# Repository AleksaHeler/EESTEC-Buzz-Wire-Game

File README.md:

# EESTEC-Buzz-Wire-Game

Buzz wire game HW for interactive booths made for EESTEC LC Novi Sad. Made in KiCAD and order from PCB manufaturer from China.

## Example

## Idea

Idea is to make a simple custom HW board for visitors to play with and learn some basic electronics examples.

Using 555 timer chip create an oscillator which beeps a piezo buzzer when wires touch.

## Execution

TODO: add images:
 - schematic
 - PCB (KiCAD view, photos of actual PCBs)
 - board, mounting of all components

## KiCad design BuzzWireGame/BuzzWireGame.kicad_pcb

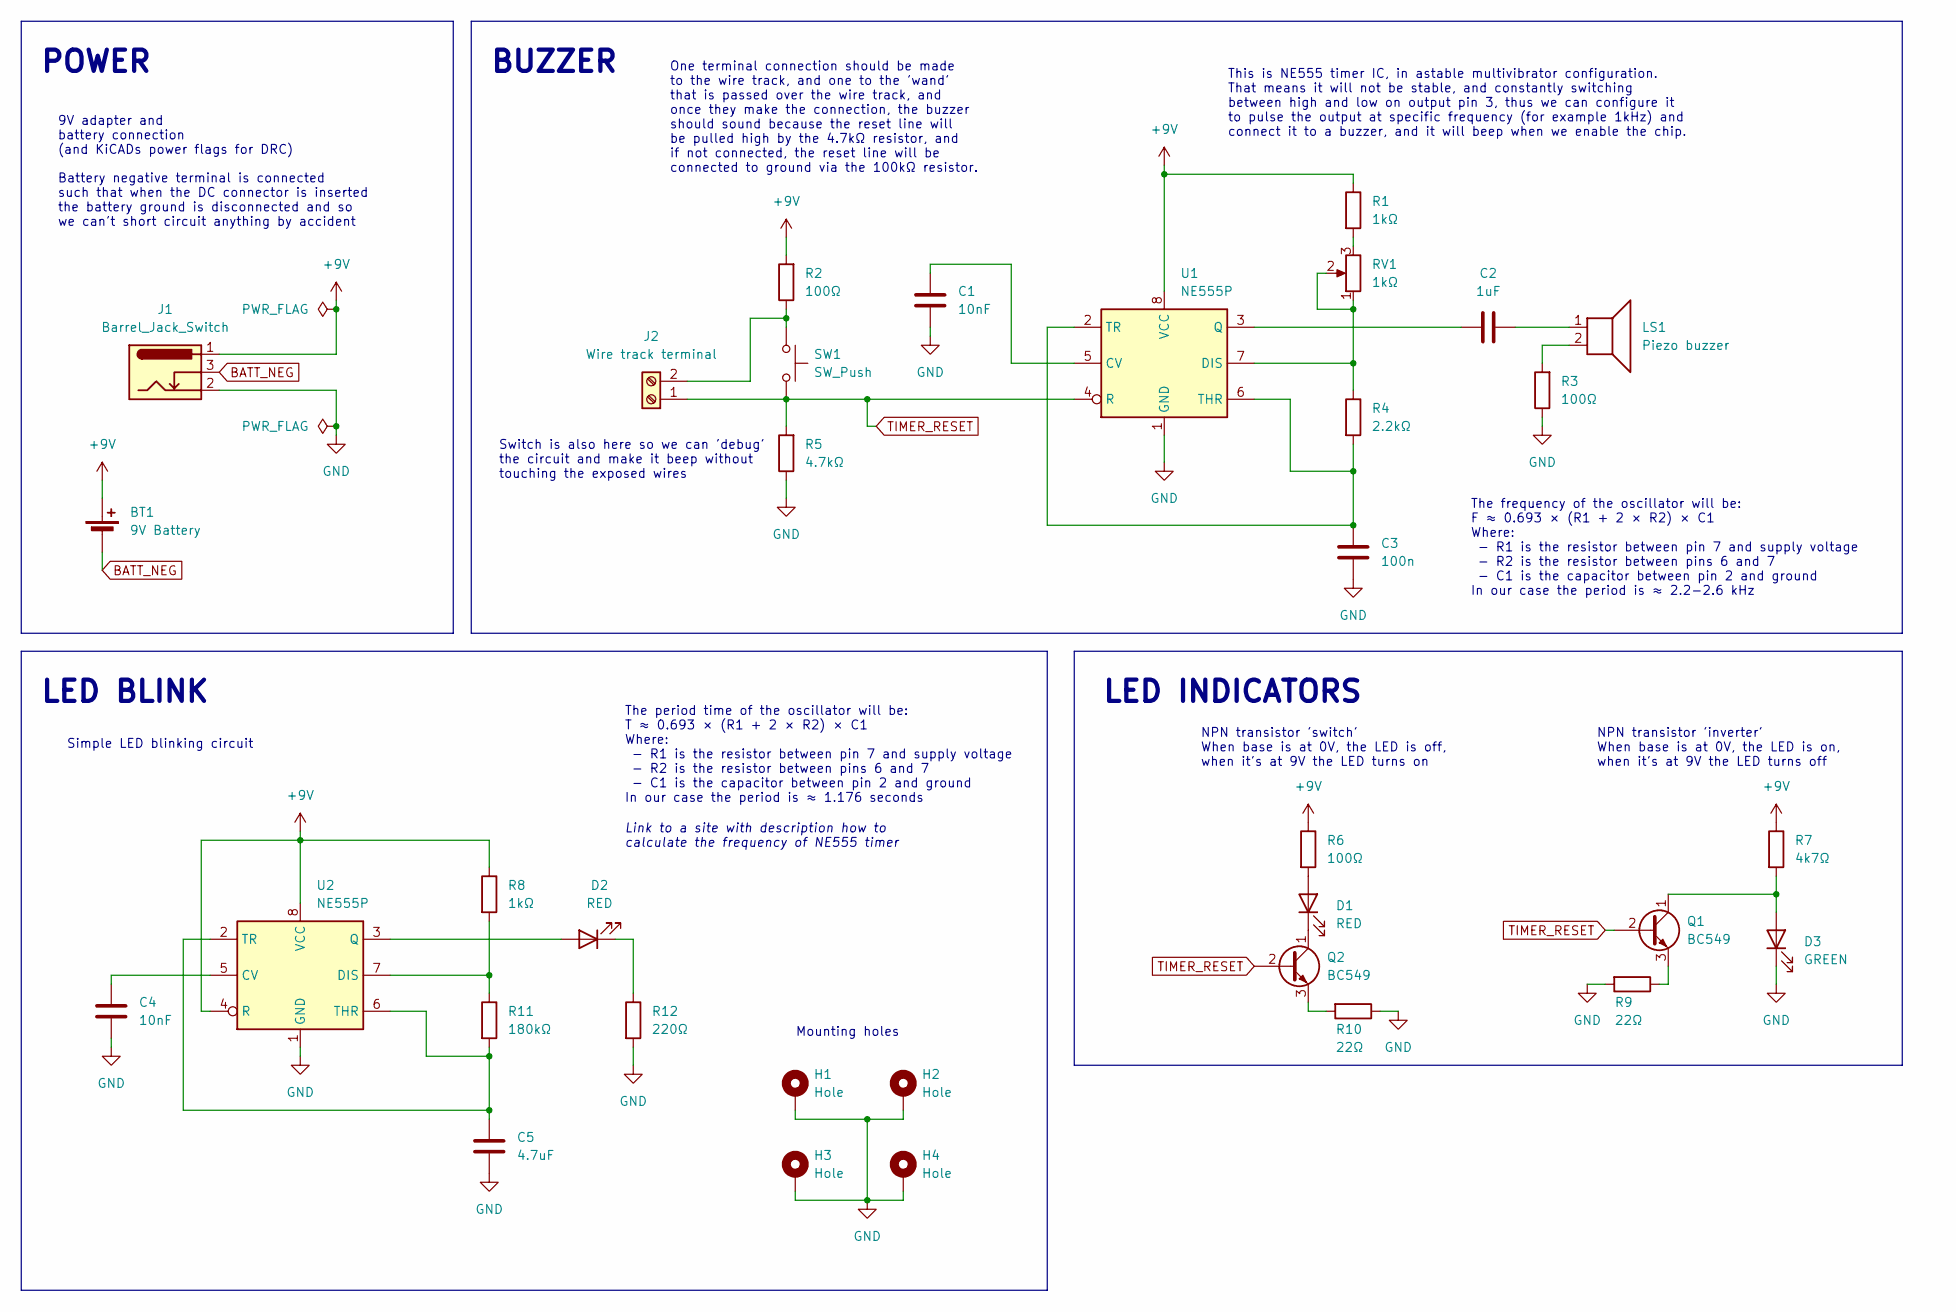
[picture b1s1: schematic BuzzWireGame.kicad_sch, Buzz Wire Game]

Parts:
BT1: 9V Battery; TerminalBlock_bornier-2_P5.08mm
C1, C4: 10nF; C_1206_3216Metric
C2: 1uF; C_1206_3216Metric
C3: 100n; C_1206_3216Metric
C5: 4.7uF; CP_Radial_D4.0mm_P2.00mm
D1, D2: RED; LED_D5.0mm_Clear
D3: GREEN; LED_D5.0mm_Clear
H1, H2, H3, H4: Hole; MountingHole_3.2mm_M3_Pad_Via
J1: Barrel_Jack_Switch; BarrelJack_Horizontal
J2: Wire track terminal; TerminalBlock_bornier-2_P5.08mm
LS1: Piezo buzzer; Indicator_PUI_AI-1440-TWT-24V-2-R
Q1, Q2: BC549; TO-92_Inline
R1, R8: 1kΩ; R_Axial_DIN0207_L6.3mm_D2.5mm_P10.16mm_Horizontal
R2, R3, R6: 100Ω; R_Axial_DIN0207_L6.3mm_D2.5mm_P10.16mm_Horizontal
R4: 2.2kΩ; R_Axial_DIN0207_L6.3mm_D2.5mm_P10.16mm_Horizontal
R5: 4.7kΩ; R_Axial_DIN0207_L6.3mm_D2.5mm_P10.16mm_Horizontal
R7: 4k7Ω; R_Axial_DIN0207_L6.3mm_D2.5mm_P10.16mm_Horizontal
R9, R10: 22Ω; R_Axial_DIN0207_L6.3mm_D2.5mm_P10.16mm_Horizontal
R11: 180kΩ; R_Axial_DIN0207_L6.3mm_D2.5mm_P10.16mm_Horizontal
R12: 220Ω; R_Axial_DIN0207_L6.3mm_D2.5mm_P10.16mm_Horizontal
RV1: 1kΩ; Potentiometer_Alps_RK163_Single_Horizontal
SW1: SW_Push; SW_PUSH_6mm_H4.3mm
U1, U2: NE555P; DIP-8_W7.62mm

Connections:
+9V: BT1.1 (+), J1.1, R1.1, R2.2, R6.1, R7.1, R8.1, U1.8 (VCC), U2.4 (R), U2.8 (VCC)
BATT_NEG: BT1.2 (-), J1.3
GND: C1.2, C3.2, C4.2, C5.2, D3.1 (K), H1.1, H2.1, H3.1, H4.1, J1.2, R3.1, R5.1, R9.2, R10.1, R12.2, U1.1 (GND), U2.1 (GND)
unnamed: C2.2, LS1.1
unnamed: D1.2 (A), R6.2
unnamed: D1.1 (K), Q2.1 (C)
unnamed: D2.2 (A), U2.3 (Q)
unnamed: D2.1 (K), R12.1
unnamed: D3.2 (A), Q1.1 (C), R7.2
unnamed: J2.2, R2.1, SW1.1
unnamed: LS1.2, R3.2
unnamed: Q1.3 (E), R9.1
unnamed: Q2.3 (E), R10.2
unnamed: R1.2, RV1.3
unnamed: C1.1, U1.5 (CV)
unnamed: R4.1, RV1.1, RV1.2, U1.7 (DIS)
unnamed: C2.1, U1.3 (Q)
unnamed: C3.1, R4.2, U1.2 (TR), U1.6 (THR)
unnamed: C4.1, U2.5 (CV)
unnamed: R8.2, R11.1, U2.7 (DIS)
unnamed: C5.1, R11.2, U2.2 (TR), U2.6 (THR)
TIMER_RESET: J2.1, Q1.2 (B), Q2.2 (B), R5.2, SW1.2, U1.4 (R)

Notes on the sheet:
LED BLINK
One terminal connection should be made to the wire track, and one to the 'wand' that is passed over the wire track, and once they make the connection, the buzzer should sound because the reset line will be pulled high by the 4.7kΩ resistor, and if not connected, the reset line will be connected to 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
Battery negative terminal is connected such that when the DC connector is inserted the battery ground is disconnected and so we can't short circuit anything by accident
POWER
9V adapter and battery connection (and KiCADs power flags for DRC)
Mounting holes
Simple LED blinking circuit
This is NE555 timer IC, in astable multivibrator configuration. That means it will not be stable, and constantly switching between high and low on output pin 3, thus we can configure it to pulse the output at specific frequency (for example 1kHz) and connect it to a buzzer, and it will beep when we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
NPN transistor 'inverter' When base is at 0V, the LED is on, when it's at 9V the LED turns off
LED INDICATORS
The frequency of the oscillator will be: F ≈ 0.693 × (R1 + 2 × R2) × C1 Where: - R1 is the resistor between pin 7 and supply voltage - R2 is the resistor between pins 6 and 7 - C1 is the capacitor between pin 2 and ground In our case the period is ≈ 2.2-2.6 kHz
BUZZER
NPN transistor 'switch' When base is at 0V, the LED is off, when it's at 9V the LED turns on
Switch is also here so we can 'debug' the circuit and make it beep without touching the exposed wires
Link to a site with description how to calculate the frequency of NE555 timer
The period time of the oscillator will be: T ≈ 0.693 × (R1 + 2 × R2) × C1 Where: - R1 is the resistor between pin 7 and supply voltage - R2 is the resistor between pins 6 and 7 - C1 is the capacitor between pin 2 and ground In our case the period is ≈ 1.176 seconds

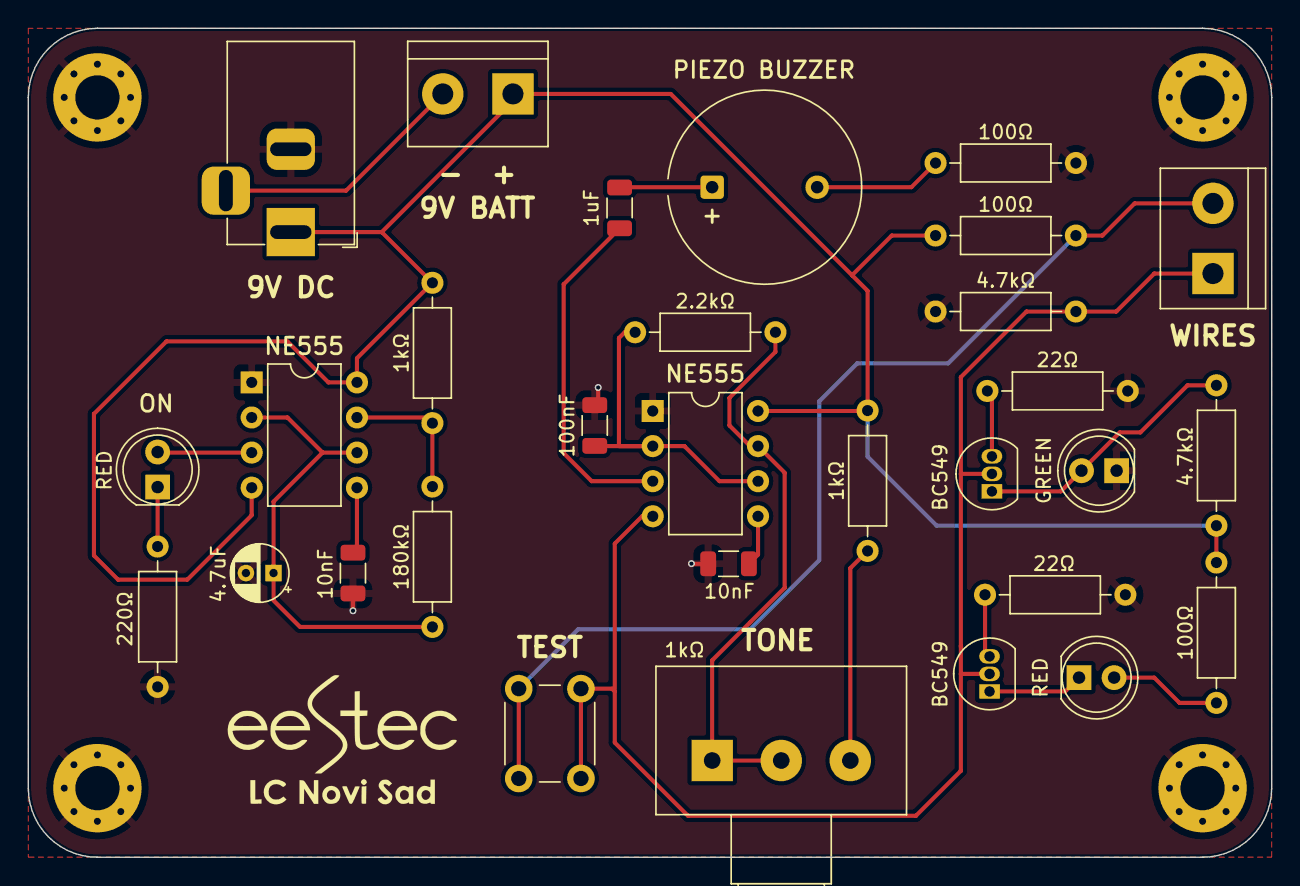
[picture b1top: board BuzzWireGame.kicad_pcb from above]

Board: 2 copper layers, 90.0 x 60.0 mm, 34 parts (0 on the bottom side), 22 nets.

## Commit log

2024-02-26 Update readme, add image
2024-02-26 Start with schematics
2024-02-27 Finish schm and PCB design for v1.0
